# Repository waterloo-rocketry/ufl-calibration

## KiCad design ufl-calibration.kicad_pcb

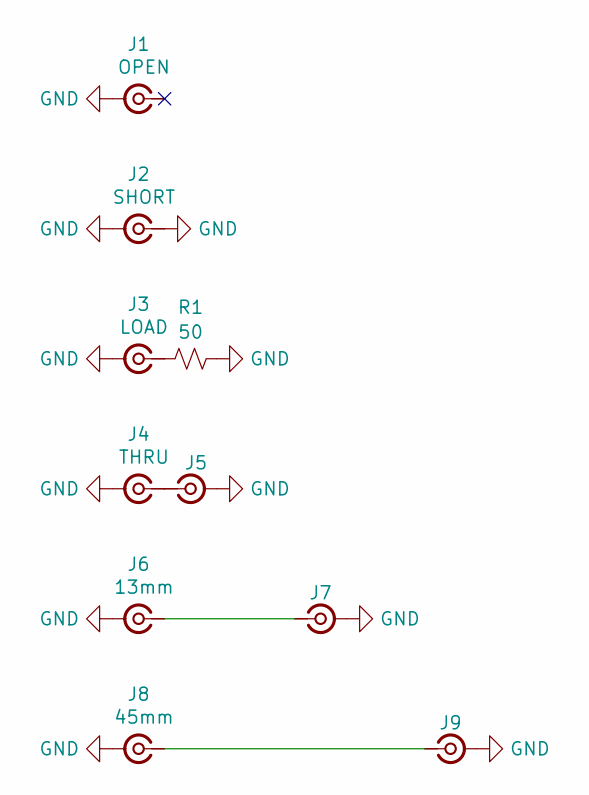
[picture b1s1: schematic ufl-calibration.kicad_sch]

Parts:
J1: OPEN; U.FL_Hirose_U.FL-R-SMT-1_Vertical
J2: SHORT; U.FL_Hirose_U.FL-R-SMT-1_Vertical
J3: LOAD; U.FL_Hirose_U.FL-R-SMT-1_Vertical
J4: THRU; U.FL_Hirose_U.FL-R-SMT-1_Vertical
J5, J7, J9: Conn_Coaxial_Small; U.FL_Hirose_U.FL-R-SMT-1_Vertical
J6: 13mm; U.FL_Hirose_U.FL-R-SMT-1_Vertical
J8: 45mm; U.FL_Hirose_U.FL-R-SMT-1_Vertical
R1: 50; R_0402_1005Metric_Pad0.72x0.64mm_HandSolder

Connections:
GND: J1.2 (Ext_2), J2.1 (In), J2.2 (Ext), J3.2 (Ext), J4.2 (Ext), J5.2 (Ext), J6.2 (Ext), J7.2 (Ext), J8.2 (Ext), J9.2 (Ext), R1.2
unnamed: J3.1 (In), R1.1
unnamed: J4.1 (In), J5.1 (In)
unnamed: J6.1 (In), J7.1 (In)
unnamed: J8.1 (In), J9.1 (In)

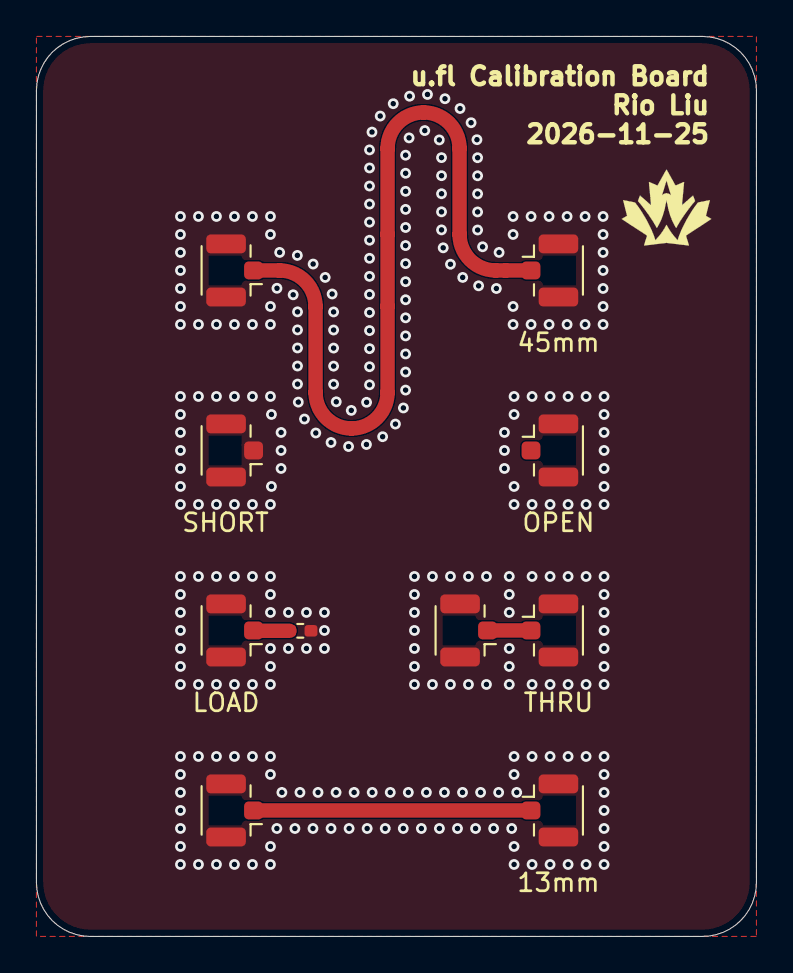
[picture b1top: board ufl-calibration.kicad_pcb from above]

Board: 2 copper layers, 40.0 x 50.0 mm, 10 parts (0 on the bottom side), 5 nets.
